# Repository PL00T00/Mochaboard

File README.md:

# Mochaboard
A keyboard. Just a keyboard...

I started designing the 'Mochaboard' (named after the best caffieneted drink) because I feel most keyboards now are full of unnescary features and don't achieve what a good keyboard is - allow for extremely fast typing. The mochaboard is purely a keyboard, nothing else. No screens, no knobs, just keys.

Project is extremely simple but sometimes it's the simplest things in life that just work... and that's what I'm looking for in a keyboard, something that works.

"The design of the keyboard was perfected like 20 years ago" - Some random person who goes to the same hackerspace as me, 2026

Now to go drink a mocha

<h2>Schematic!</h2><br><br>
<p>The schematic is quite simple with just a key matrix and the Pi Pico. This is good, simple is good.</p>

<br><br>

<h2>PCB!</h2><br><br>
<p>The PCB is also simple with a very basic layout and a small silk-screen coffee cup. Sometimes you just have to purely focus on one feature (typing) and ignore or entirely leave out any bells and whistles. </p>

<br><br>

<h2>Case!</h2><br><br>
<p>The case is simple. It is set up for sandwich mounting because of the simplicity of sandwich mounting. It has holes for all the keys, one for the Pico and and last one to show off the silkscreen.</p>

<br><br>

<h2>firmware...</h2><br><br>
<p>Firmware is probably my second-to-least favourite thing in the world, because of how complicated it is. Because of my smol brain I did enlist the help of some AI to assist in making the firmware. I attempted to make the QMK firmware as simple as possible and include all comments from the AI so if I do realise I need to change something I could atleast be looking in the right spot. It's all a learning experience I guess, maybe one day I'll enjoy doing this, just definitely not today</p><br><br>
<h2>BOM</h2>

| Reference | Qty | Value | DNP | Exclude from BOM | Exclude from Board | Footprint | Datasheet |
|---|---:|---|---|---|---|---|---|
| A1 | 1 | RaspberryPi_Pico |  |  |  | Module:RaspberryPi_Pico_Common_THT | https://datasheets.raspberrypi.com/pico/pico-datasheet.pdf |
| D1,D2,D3,D4,D5,D6,D7,D8,D9,D10,D11,D12,D13,D14,D15,D16,D17,D18,D19,D20,D21,D22,D23,D24,D25,D26,D27,D28,D29,D30,D31,D32,D33,D34,D35,D36,D37,D38,D39,D40,D41,D42,D43,D44,D45,D46,D47,D48,D49,D50,D51,D52,D53,D54,D55,D56,D57,D58,D59,D60,D61 | 61 | 1N4148 |  |  |  | Diode_THT:D_DO-35_SOD27_P7.62mm_Horizontal | https://assets.nexperia.com/documents/data-sheet/1N4148_1N4448.pdf |
| S1 | 1 | MX_stab |  |  |  | PCM_marbastlib-mx:STAB_MX_P_2u |  |
| S2,S3 | 2 | MX_stab |  |  |  | PCM_marbastlib-mx:STAB_MX_2.25u |  |
| S4 | 1 | MX_stab |  |  |  | PCM_marbastlib-mx:STAB_MX_2.75u |  |
| S5 | 1 | MX_stab |  |  |  | PCM_marbastlib-mx:STAB_MX_P_6.25u |  |
| SW1,SW2,SW3,SW4,SW5,SW6,SW7,SW8,SW9,SW10,SW11,SW12,SW13,SW14,SW15,SW16,SW17,SW18,SW19,SW20,SW21,SW22,SW23,SW24,SW25,SW26,SW27,SW28,SW29,SW30,SW31,SW32,SW33,SW34,SW35,SW36,SW37,SW38,SW39,SW40,SW41,SW42,SW43,SW44,SW45,SW46,SW47,SW48,SW49,SW50,SW51,SW52,SW53,SW54,SW55,SW56,SW57,SW58,SW59,SW60,SW61 | 61 | SW_Push |  |  |  | PCM_marbastlib-mx:SW_MX_1u |  |

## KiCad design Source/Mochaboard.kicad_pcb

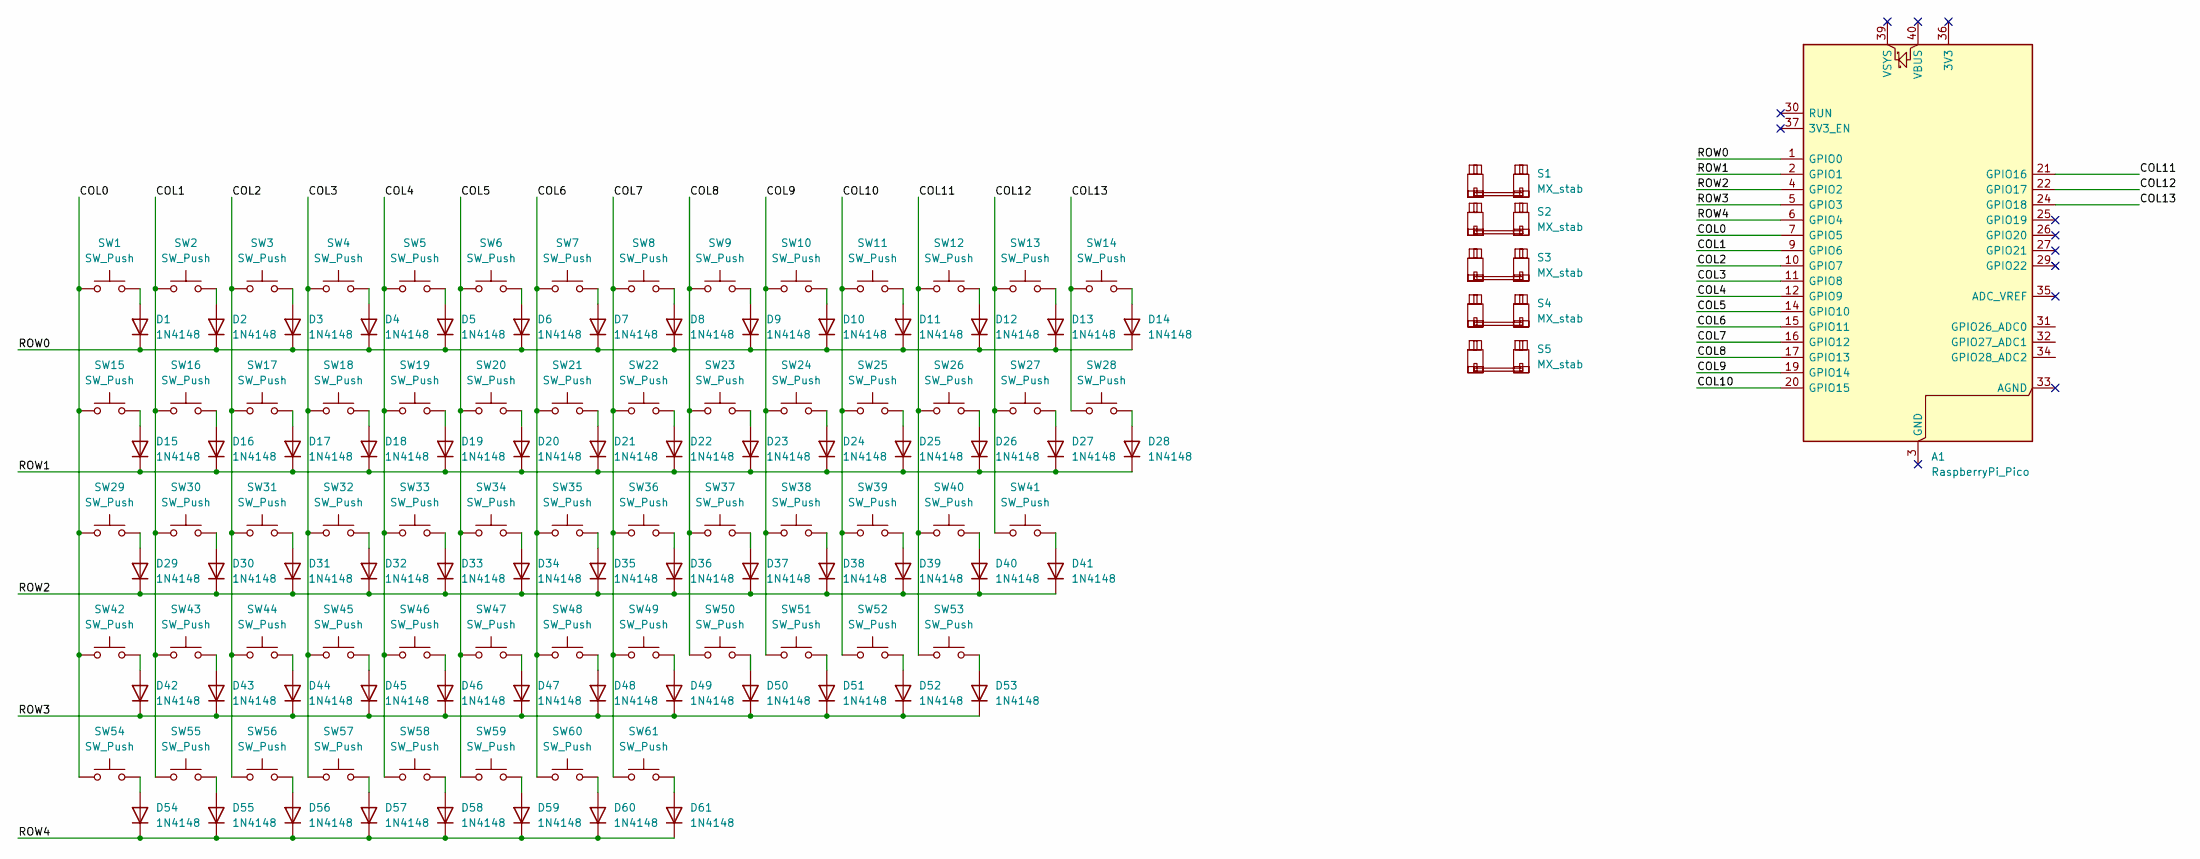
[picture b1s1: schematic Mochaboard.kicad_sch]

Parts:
A1: RaspberryPi_Pico; RaspberryPi_Pico_Common_THT
D1, D2, D3, D4, D5, D6, D7, D8, D9, D10, D11, D12, D13, D14, D15, D16, D17, D18, D19, D20, D21, D22, D23, D24, D25, D26, D27, D28, D29, D30, D31, D32, D33, D34, D35, D36, D37, D38, D39, D40, D41, D42, D43, D44, D45, D46, D47, D48, D49, D50, D51, D52, D53, D54, D55, D56, D57, D58, D59, D60, D61: 1N4148; D_DO-35_SOD27_P7.62mm_Horizontal
S1: MX_stab; STAB_MX_P_2u
S2, S3: MX_stab; STAB_MX_2.25u
S4: MX_stab; STAB_MX_2.75u
S5: MX_stab; STAB_MX_P_6.25u
SW1, SW2, SW3, SW4, SW5, SW6, SW7, SW8, SW9, SW10, SW11, SW12, SW13, SW14, SW15, SW16, SW17, SW18, SW19, SW20, SW21, SW22, SW23, SW24, SW25, SW26, SW27, SW28, SW29, SW30, SW31, SW32, SW33, SW34, SW35, SW36, SW37, SW38, SW39, SW40, SW41, SW42, SW43, SW44, SW45, SW46, SW47, SW48, SW49, SW50, SW51, SW52, SW53, SW54, SW55, SW56, SW57, SW58, SW59, SW60, SW61: SW_Push; SW_MX_1u

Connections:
/COL0: A1.7 (GPIO5), SW1.1, SW15.1, SW29.1, SW42.1, SW54.1
/COL1: A1.9 (GPIO6), SW2.1, SW16.1, SW30.1, SW43.1, SW55.1
/COL2: A1.10 (GPIO7), SW3.1, SW17.1, SW31.1, SW44.1, SW56.1
/COL3: A1.11 (GPIO8), SW4.1, SW18.1, SW32.1, SW45.1, SW57.1
/COL4: A1.12 (GPIO9), SW5.1, SW19.1, SW33.1, SW46.1, SW58.1
/COL5: A1.14 (GPIO10), SW6.1, SW20.1, SW34.1, SW47.1, SW59.1
/COL6: A1.15 (GPIO11), SW7.1, SW21.1, SW35.1, SW48.1, SW60.1
/COL7: A1.16 (GPIO12), SW8.1, SW22.1, SW36.1, SW49.1, SW61.1
/COL8: A1.17 (GPIO13), SW9.1, SW23.1, SW37.1, SW50.1
/COL9: A1.19 (GPIO14), SW10.1, SW24.1, SW38.1, SW51.1
/COL10: A1.20 (GPIO15), SW11.1, SW25.1, SW39.1, SW52.1
/COL11: A1.21 (GPIO16), SW12.1, SW26.1, SW40.1, SW53.1
/COL12: A1.22 (GPIO17), SW13.1, SW27.1, SW41.1
/COL13: A1.24 (GPIO18), SW14.1, SW28.1
/ROW0: A1.1 (GPIO0), D1.1 (K), D2.1 (K), D3.1 (K), D4.1 (K), D5.1 (K), D6.1 (K), D7.1 (K), D8.1 (K), D9.1 (K), D10.1 (K), D11.1 (K), D12.1 (K), D13.1 (K), D14.1 (K)
/ROW1: A1.2 (GPIO1), D15.1 (K), D16.1 (K), D17.1 (K), D18.1 (K), D19.1 (K), D20.1 (K), D21.1 (K), D22.1 (K), D23.1 (K), D24.1 (K), D25.1 (K), D26.1 (K), D27.1 (K), D28.1 (K)
/ROW2: A1.4 (GPIO2), D29.1 (K), D30.1 (K), D31.1 (K), D32.1 (K), D33.1 (K), D34.1 (K), D35.1 (K), D36.1 (K), D37.1 (K), D38.1 (K), D39.1 (K), D40.1 (K), D41.1 (K)
/ROW3: A1.5 (GPIO3), D42.1 (K), D43.1 (K), D44.1 (K), D45.1 (K), D46.1 (K), D47.1 (K), D48.1 (K), D49.1 (K), D50.1 (K), D51.1 (K), D52.1 (K), D53.1 (K)
/ROW4: A1.6 (GPIO4), D54.1 (K), D55.1 (K), D56.1 (K), D57.1 (K), D58.1 (K), D59.1 (K), D60.1 (K), D61.1 (K)
unnamed: D1.2 (A), SW1.2
unnamed: D2.2 (A), SW2.2
unnamed: D3.2 (A), SW3.2
unnamed: D4.2 (A), SW4.2
unnamed: D5.2 (A), SW5.2
unnamed: D6.2 (A), SW6.2
unnamed: D7.2 (A), SW7.2
unnamed: D8.2 (A), SW8.2
unnamed: D9.2 (A), SW9.2
unnamed: D10.2 (A), SW10.2
unnamed: D11.2 (A), SW11.2
unnamed: D12.2 (A), SW12.2
unnamed: D13.2 (A), SW13.2
unnamed: D14.2 (A), SW14.2
unnamed: D15.2 (A), SW15.2
unnamed: D16.2 (A), SW16.2
unnamed: D17.2 (A), SW17.2
unnamed: D18.2 (A), SW18.2
unnamed: D19.2 (A), SW19.2
unnamed: D20.2 (A), SW20.2
unnamed: D21.2 (A), SW21.2
unnamed: D22.2 (A), SW22.2
unnamed: D23.2 (A), SW23.2
unnamed: D24.2 (A), SW24.2
unnamed: D25.2 (A), SW25.2
unnamed: D26.2 (A), SW26.2
unnamed: D27.2 (A), SW27.2
unnamed: D28.2 (A), SW28.2
unnamed: D29.2 (A), SW29.2
unnamed: D30.2 (A), SW30.2
unnamed: D31.2 (A), SW31.2
unnamed: D32.2 (A), SW32.2
unnamed: D33.2 (A), SW33.2
unnamed: D34.2 (A), SW34.2
unnamed: D35.2 (A), SW35.2
unnamed: D36.2 (A), SW36.2
unnamed: D37.2 (A), SW37.2
unnamed: D38.2 (A), SW38.2
unnamed: D39.2 (A), SW39.2
unnamed: D40.2 (A), SW40.2
unnamed: D41.2 (A), SW41.2
unnamed: D42.2 (A), SW42.2
unnamed: D43.2 (A), SW43.2
unnamed: D44.2 (A), SW44.2
unnamed: D45.2 (A), SW45.2
unnamed: D46.2 (A), SW46.2
unnamed: D47.2 (A), SW47.2
unnamed: D48.2 (A), SW48.2
unnamed: D49.2 (A), SW49.2
unnamed: D50.2 (A), SW50.2
unnamed: D51.2 (A), SW51.2
unnamed: D52.2 (A), SW52.2
unnamed: D53.2 (A), SW53.2
unnamed: D54.2 (A), SW54.2
unnamed: D55.2 (A), SW55.2
unnamed: D56.2 (A), SW56.2
unnamed: D57.2 (A), SW57.2
unnamed: D58.2 (A), SW58.2
unnamed: D59.2 (A), SW59.2
unnamed: D60.2 (A), SW60.2
unnamed: D61.2 (A), SW61.2

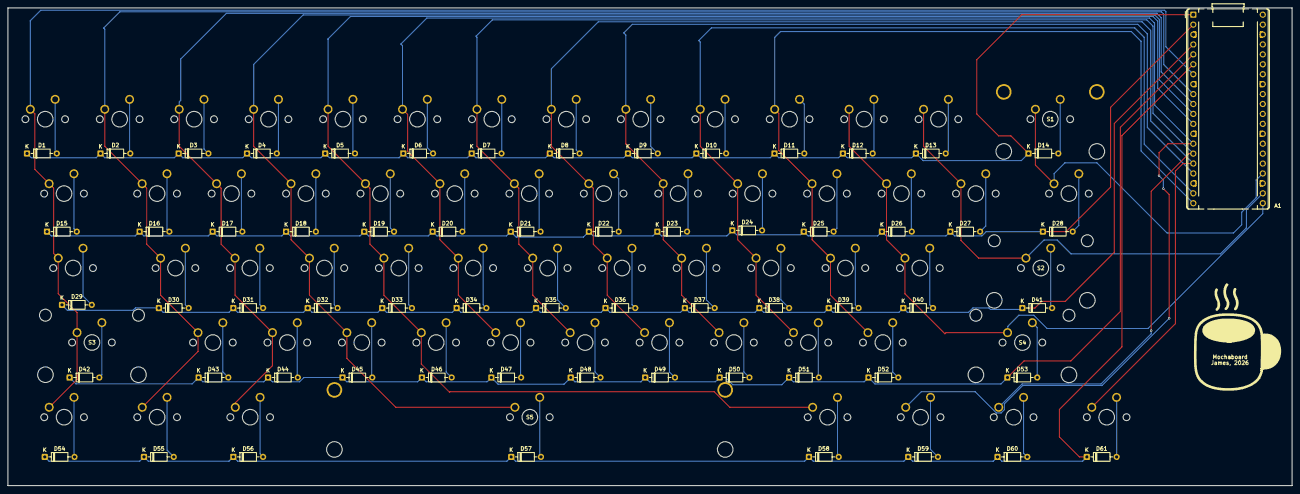
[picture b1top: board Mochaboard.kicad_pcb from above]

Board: 2 copper layers, 328.7 x 122.2 mm, 128 parts (0 on the bottom side), 80 nets.

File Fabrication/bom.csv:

Designator,Footprint,Quantity,Value,LCSC Part #
A1,RaspberryPi_Pico_Common_THT,1,RaspberryPi_Pico,
"D1, D10, D11, D12, D13, D14, D15, D16, D17, D18, D19, D2, D20, D21, D22, D23, D24, D25, D26, D27, D28, D29, D3, D30, D31, D32, D33, D34, D35, D36, D37, D38, D39, D4, D40, D41, D42, D43, D44, D45, D46, D47, D48, D49, D5, D50, D51, D52, D53, D54, D55, D56, D57, D58, D59, D6, D60, D61, D7, D8, D9",D_DO-35_SOD27_P7.62mm_Horizontal,61,1N4148,
S1,STAB_MX_P_2u,1,MX_stab,
"S2, S3",STAB_MX_2.25u,2,MX_stab,
S4,STAB_MX_2.75u,1,MX_stab,
S5,STAB_MX_P_6.25u,1,MX_stab,
"SW1, SW10, SW11, SW12, SW13, SW14, SW15, SW16, SW17, SW18, SW19, SW2, SW20, SW21, SW22, SW23, SW24, SW25, SW26, SW27, SW28, SW29, SW3, SW30, SW31, SW32, SW33, SW34, SW35, SW36, SW37, SW38, SW39, SW4, SW40, SW41, SW42, SW43, SW44, SW45, SW46, SW47, SW48, SW49, SW5, SW50, SW51, SW52, SW53, SW54, SW55, SW56, SW57, SW58, SW59, SW6, SW60, SW61, SW7, SW8, SW9",SW_MX_1u,61,SW_Push,
